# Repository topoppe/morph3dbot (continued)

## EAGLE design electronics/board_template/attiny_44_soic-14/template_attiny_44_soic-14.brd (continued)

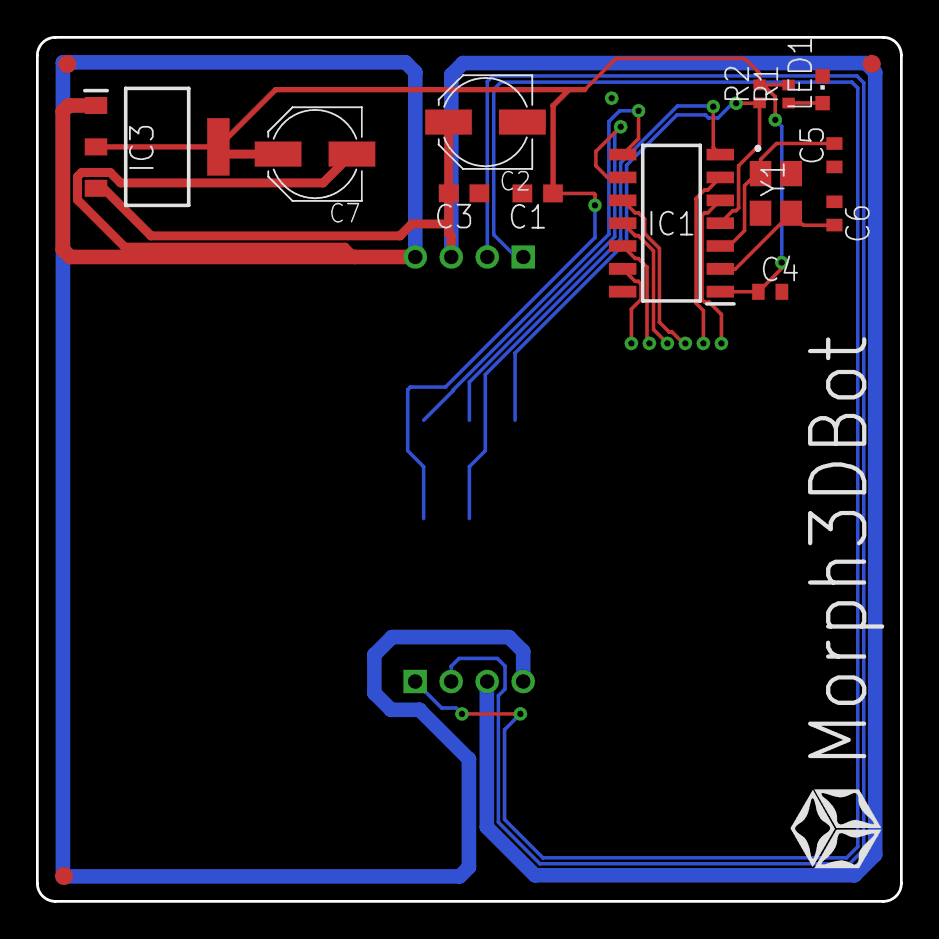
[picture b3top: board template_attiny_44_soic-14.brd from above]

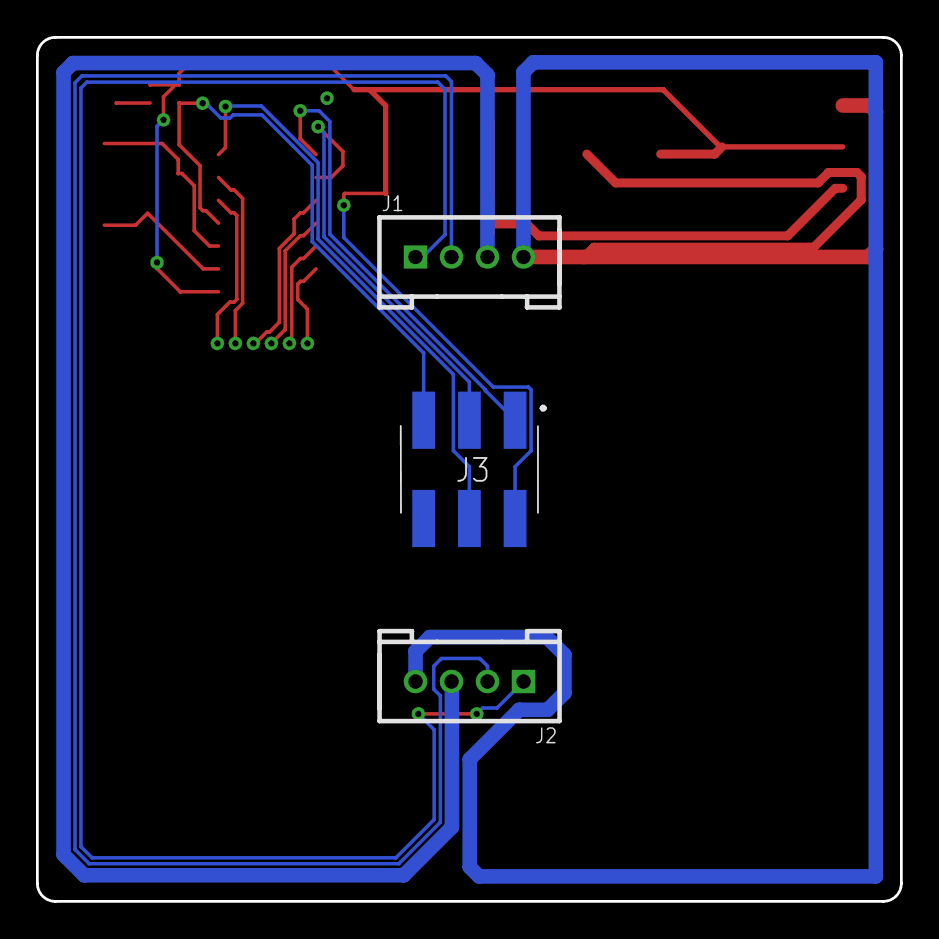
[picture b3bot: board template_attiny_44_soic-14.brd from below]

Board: 2 copper layers, 48.0 x 48.0 mm, 20 parts (3 on the bottom side), 12 nets.

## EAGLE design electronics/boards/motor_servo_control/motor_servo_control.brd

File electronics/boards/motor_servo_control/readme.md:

# Motor- und Servoplatine
Die Motor- und Servoplatine besitzt keinen eigenen Controller. Statt ihrer ist ein I2C-Portexpander [PCA9685](https://www.nxp.com/docs/en/data-sheet/PCA9685.pdf) von NXP verbaut.
Die I2C-Adresse lässt sich über einen DIP-Schalter einstellen.

Die Servo-Anschlüsse sind mit den Ausgängen LED8 bis LED15 verbunden.
Über der Anschlussleiste der Servos kann man mit Hilfe eines Jumpers einstellen, ob die Servos mit Systemspannung oder mit 5V versorgt werden sollen.

Auf der Motor-Platine ist außerdem noch ein Motortreiber [TB6612FNG](https://toshiba.semicon-storage.com/info/docget.jsp?did=10660&prodName=TB6612FNG) von Toshiba verbaut.
An ihm können zwei Gleichstrommotoren angeschlossen werden. Die Verbindung zum Portexpander-Chip lautet:

- TB6612FNG PWM-A = PCA9685 PWM2
- TB6612FNG A-IN-1 = PCA9685 PWM4
- TB6612FNG A-IN-2 = PCA9685 PWM3
- TB6612FNG PWM-B = PCA9685 PWM7
- TB6612FNG B-IN-1 = PCA9685 PWM6
- TB6612FNG B-IN-2 = PCA9685 PWM5

Die DC-Motoren werden hierbei duch die Systemspannung versorgt.

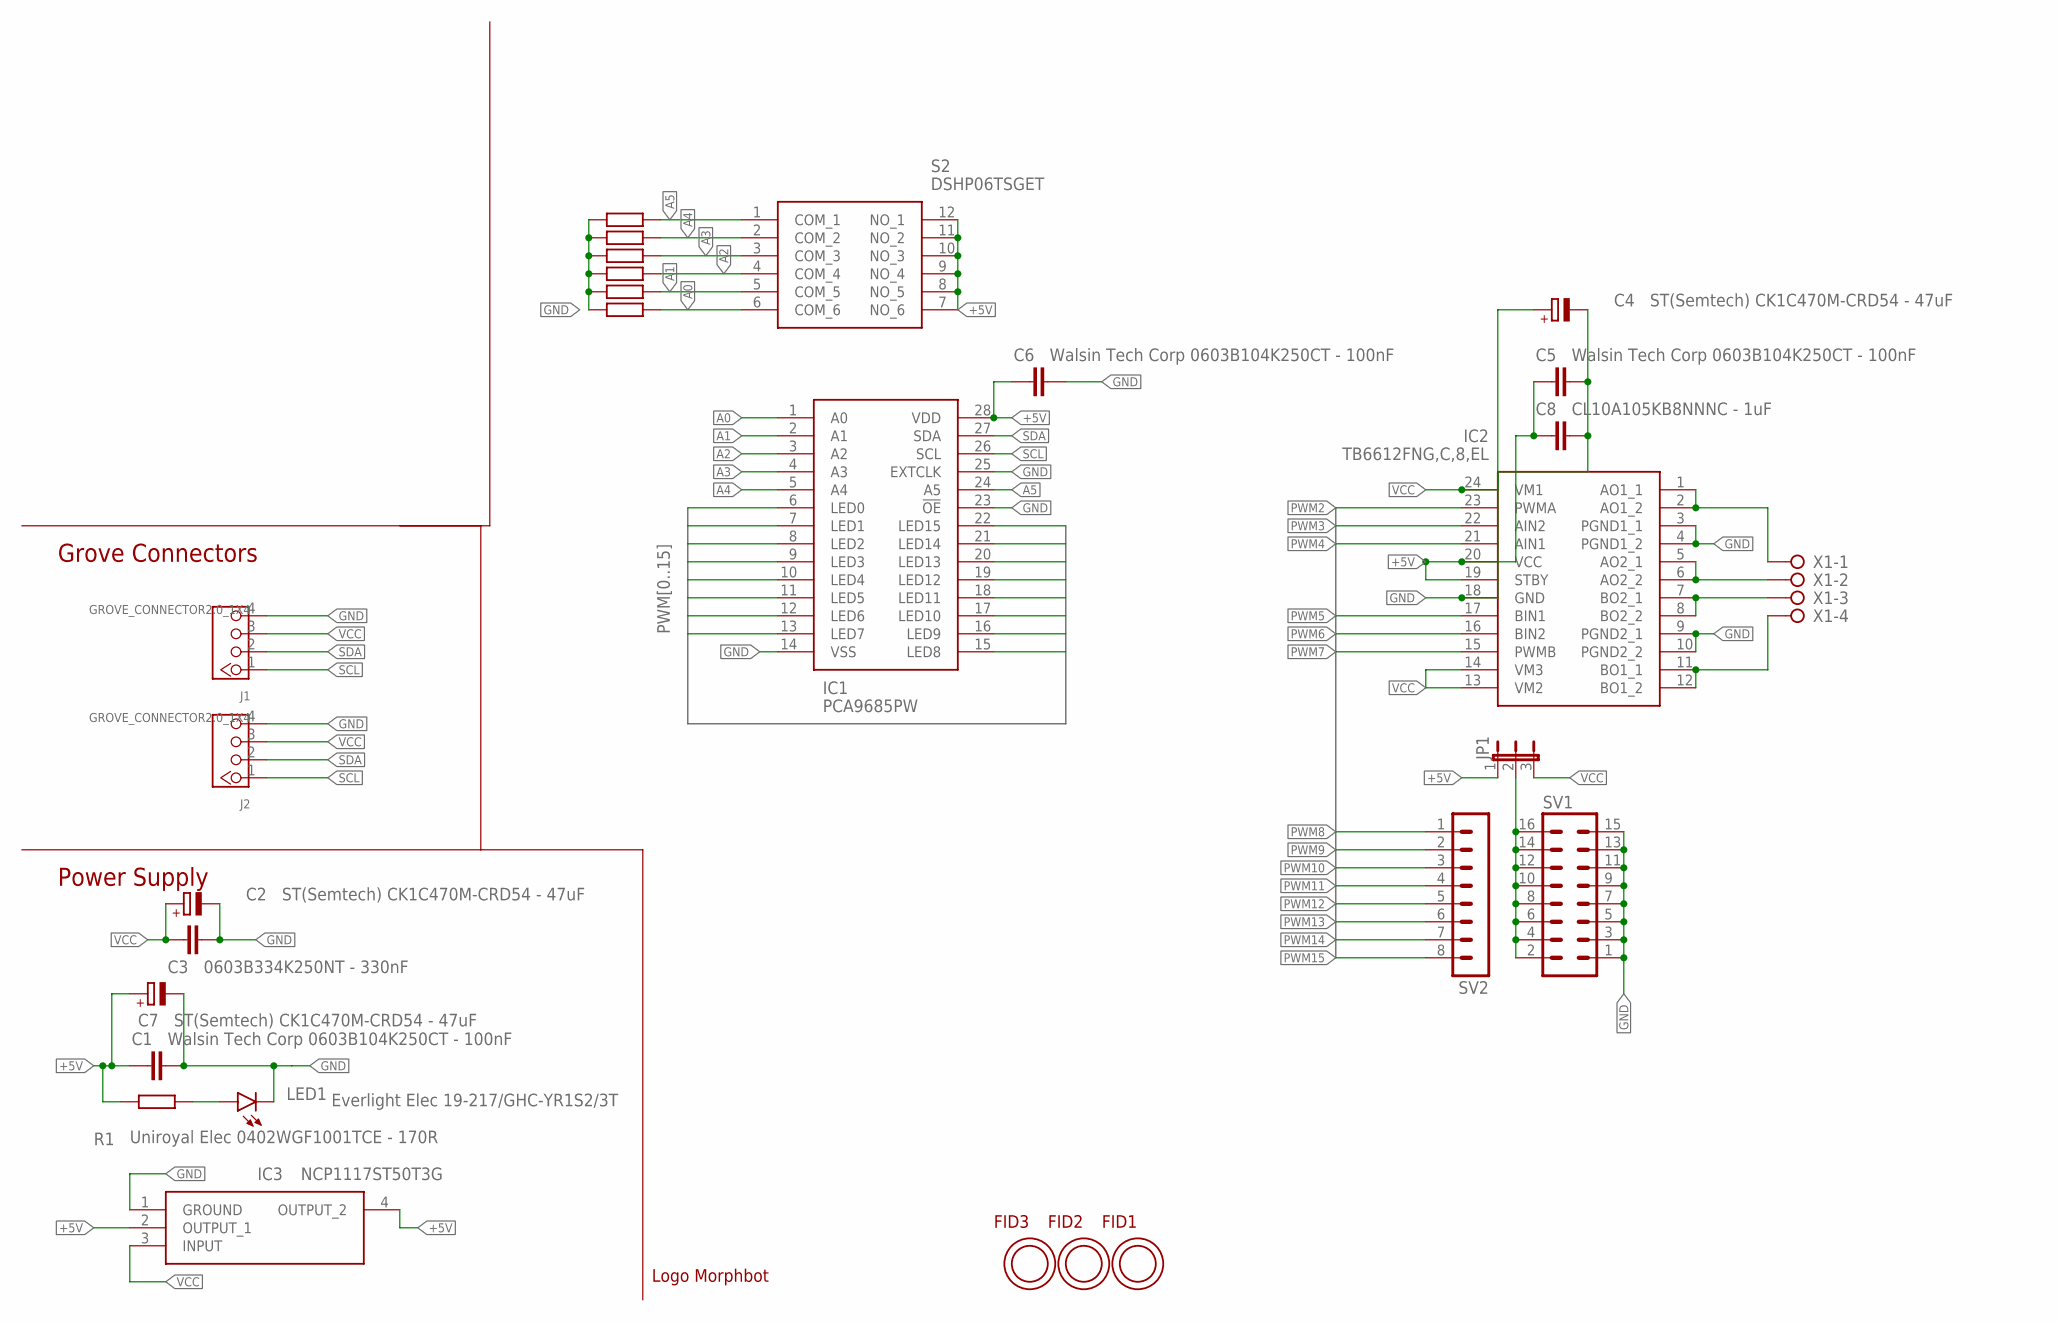
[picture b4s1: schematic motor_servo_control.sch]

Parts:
C1, C5, C6: Walsin Tech Corp 0603B104K250CT - 100nF; C0603
C2, C4, C7: ST(Semtech) CK1C470M-CRD54 - 47uF; PANASONIC_C
C3: 0603B334K250NT - 330nF; C0603
C8: CL10A105KB8NNNC - 1uF; C0603
FID1, FID2, FID3: OPEN-PNP-FIDUCIAL
IC1: PCA9685PW; SOP65P640X110-28N
IC2: TB6612FNG,C,8,EL; SOP65P760X160-24N
IC3: NCP1117ST50T3G; SOT230P700X180-4N
J1, J2: GROVE_CONNECTOR2.0_1X4; 2.0_1X4_STRAIGHT
JP1: JP2E; JP2
LED1: Everlight Elec 19-217/GHC-YR1S2/3T; CHIPLED_0603
R1: Uniroyal Elec 0402WGF1001TCE - 170R; R0402
R2, R3, R4, R5, R6, R7: 0402WGF1002TCE - 10k; R0402
S2: DSHP06TSGET
SV1: MA08-2
SV2: MA08-1
U$1: LOGO_MORPHBOT5MM; LOGO_MORPHBOT
X1: W237-04P; W237-4P

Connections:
+5V: C1.1, C5.1, C6.1, C7.+, C8.1, IC1.28 (VDD), IC2.19 (STBY), IC2.20 (VCC), IC3.2 (OUTPUT_1), IC3.4 (OUTPUT_2), JP1.1, R1.2, S2.7 (NO_6), S2.8 (NO_5), S2.9 (NO_4), S2.10 (NO_3), S2.11 (NO_2), S2.12 (NO_1)
A0: IC1.1 (A0), R7.1, S2.6 (COM_6)
A1: IC1.2 (A1), R6.1, S2.5 (COM_5)
A2: IC1.3 (A2), R5.1, S2.4 (COM_4)
A3: IC1.4 (A3), R4.1, S2.3 (COM_3)
A4: IC1.5 (A4), R3.1, S2.2 (COM_2)
A5: IC1.24 (A5), R2.1, S2.1 (COM_1)
GND: C1.2, C2.-, C3.1, C4.-, C5.2, C6.2, C7.-, C8.2, IC1.14 (VSS), IC1.23 (!OE), IC1.25 (EXTCLK), IC2.3 (PGND1_1), IC2.4 (PGND1_2), IC2.9 (PGND2_1), IC2.10 (PGND2_2), IC2.18 (GND), IC3.1 (GROUND), J1.4, J2.4, LED1.C, R2.2, R3.2, R4.2, R5.2, R6.2, R7.2, SV1.1, SV1.3, SV1.5, SV1.7, SV1.9, SV1.11, SV1.13, SV1.15
M1+: IC2.1 (AO1_1), IC2.2 (AO1_2), X1.1
M1-: IC2.5 (AO2_1), IC2.6 (AO2_2), X1.2
M2+: IC2.7 (BO2_1), IC2.8 (BO2_2), X1.3
M2-: IC2.11 (BO1_1), IC2.12 (BO1_2), X1.4
unnamed: LED1.A, R1.1
unnamed: JP1.2, SV1.2, SV1.4, SV1.6, SV1.8, SV1.10, SV1.12, SV1.14, SV1.16
PWM0: IC1.6 (LED0)
PWM1: IC1.7 (LED1)
PWM2: IC1.8 (LED2), IC2.23 (PWMA)
PWM3: IC1.9 (LED3), IC2.22 (AIN2)
PWM4: IC1.10 (LED4), IC2.21 (AIN1)
PWM5: IC1.11 (LED5), IC2.17 (BIN1)
PWM6: IC1.12 (LED6), IC2.16 (BIN2)
PWM7: IC1.13 (LED7), IC2.15 (PWMB)
PWM8: IC1.15 (LED8), SV2.1
PWM9: IC1.16 (LED9), SV2.2
PWM10: IC1.17 (LED10), SV2.3
PWM11: IC1.18 (LED11), SV2.4
PWM12: IC1.19 (LED12), SV2.5
PWM13: IC1.20 (LED13), SV2.6
PWM14: IC1.21 (LED14), SV2.7
PWM15: IC1.22 (LED15), SV2.8
SCL: IC1.26 (SCL), J1.1, J2.1
SDA: IC1.27 (SDA), J1.2, J2.2
VCC: C2.+, C3.2, C4.+, IC2.13 (VM2), IC2.14 (VM3), IC2.24 (VM1), IC3.3 (INPUT), J1.3, J2.3, JP1.3

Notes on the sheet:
Power Supply
Grove Connectors

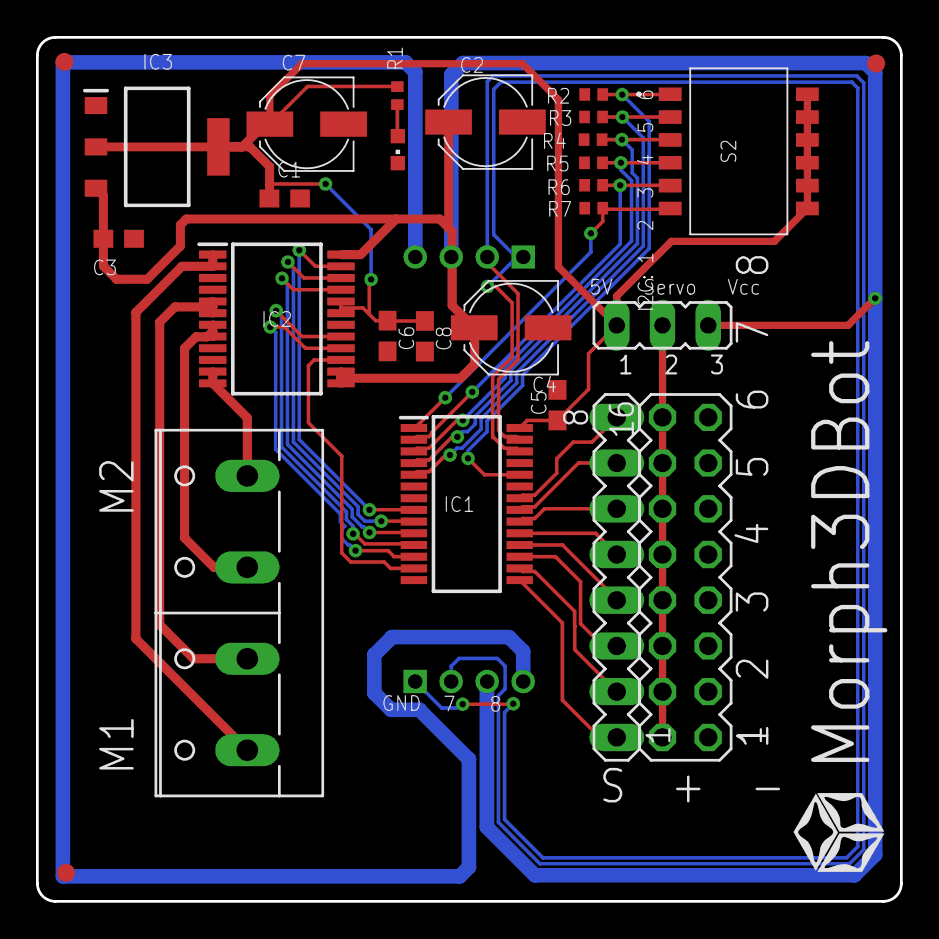
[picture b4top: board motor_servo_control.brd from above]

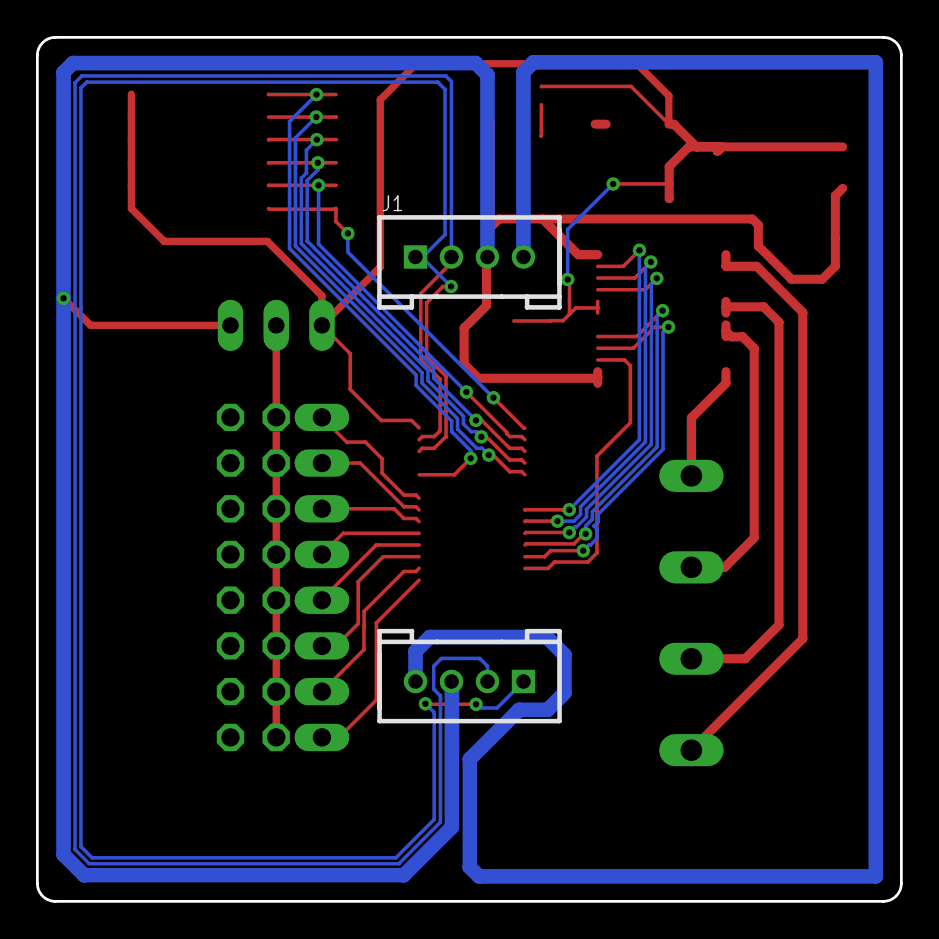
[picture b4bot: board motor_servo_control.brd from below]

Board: 2 copper layers, 48.0 x 48.0 mm, 30 parts (2 on the bottom side), 31 nets.

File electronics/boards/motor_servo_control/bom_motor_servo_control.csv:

"Qty";"Value";"Device";"Package";"Parts";"Description";"ARROW_PART_NUMBER";"ARROW_PRICE-STOCK";"DESCRIPTION";"HEIGHT";"MANUFACTURER_NAME";"MANUFACTURER_PART_NUMBER";"MF";"MOUSER_PART_NUMBER";"MOUSER_PRICE-STOCK";"MPN";"OC_FARNELL";"OC_NEWARK";"POPULARITY";"SPICEPREFIX";
"1";"";"JP2E";"JP2";"JP1";"JUMPER";"";"";"";"";"";"";"";"";"";"";"";"";"34";"";
"1";"";"MA08-1";"MA08-1";"SV2";"PIN HEADER";"";"";"";"";"";"";"";"";"";"";"unknown";"unknown";"10";"";
"1";"";"MA08-2";"MA08-2";"SV1";"PIN HEADER";"";"";"";"";"";"";"";"";"";"";"unknown";"unknown";"0";"";
"1";"";"W237-04P";"W237-4P";"X1";"WAGO SREW CLAMP";"";"";"";"";"";"";"";"";"";"";"unknown";"unknown";"2";"";
"6";"0402WGF1002TCE - 10k";"R-EU_R0402";"R0402";"R2, R3, R4, R5, R6, R7";"RESISTOR, European symbol";"";"";"";"";"";"";"";"";"";"";"";"";"0";"R";
"1";"0603B334K250NT - 330nF";"C-EUC0603";"C0603";"C3";"CAPACITOR, European symbol";"";"";"";"";"";"";"";"";"";"";"";"";"73";"C";
"1";"CL10A105KB8NNNC - 1uF";"C-EUC0603";"C0603";"C8";"CAPACITOR, European symbol";"";"";"";"";"";"";"";"";"";"";"";"";"73";"C";
"1";"DSHP06TSGET";"DSHP06TSGET";"DSHP06TSGET";"S2";"SPST 6 1.27mm, Half Slide (Standard) Black SMD DIP Switches";"";"";"SPST 6 1.27mm, Half Slide (Standard) Black SMD DIP Switches";"2.6mm";"Dongguan Guangzhu Industrial";"DSHP06TSGET";"";"";"";"";"";"";"";"";
"1";"Everlight Elec 19-217/GHC-YR1S2/3T";"LEDCHIPLED_0603";"CHIPLED_0603";"LED1";"LED";"";"";"";"";"";"";"";"";"";"";"";"";"28";"";
"2";"GROVE_CONNECTOR2.0_1X4";"GROVE_CONNECTOR2.0_1X4";"2.0_1X4_STRAIGHT";"J1, J2";"Seeedstudio Grove-Connector:";"";"";"";"";"";"";"";"";"";"";"";"";"";"";
"1";"LOGO_MORPHBOT5MM";"LOGO_MORPHBOT5MM";"LOGO_MORPHBOT";"U$1";"";"";"";"";"";"";"";"";"";"";"";"";"";"";"";
"1";"NCP1117ST50T3G";"NCP1117ST50T3G";"SOT230P700X180-4N";"IC3";"ON SEMICONDUCTOR - NCP1117ST50T3G - LDO, REG, 20VIN, 1A, 5V, 1%, SOT223-3";"NCP1117ST50T3G";"https://www.arrow.com/en/products/ncp1117st50t3g/on-semiconductor";"ON SEMICONDUCTOR - NCP1117ST50T3G - LDO, REG, 20VIN, 1A, 5V, 1%, SOT223-3";"1.8mm";"ON Semiconductor";"NCP1117ST50T3G";"";"863-NCP1117ST50T3G";"https://www.mouser.co.uk/ProductDetail/ON-Semiconductor/NCP1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";"";"";"";"";"";
"3";"OPEN-PNP-FIDUCIAL";"OPEN-PNP-FIDUCIAL";"OPEN-PNP-FIDUCIAL";"FID1, FID2, FID3";"";"";"";"";"";"";"";"";"";"";"";"";"";"";"";
"1";"PCA9685PW";"PCA9685PW";"SOP65P640X110-28N";"IC1";"LED DRIVER, RGBA, 28-TSSOP";"";"";"LED DRIVER, RGBA, 28-TSSOP";"1.1mm";"Nexperia";"PCA9685PW";"";"N/A";"https://www.mouser.com/Search/Refine.aspx?Keyword=N%2FA";"";"";"";"";"";
"3";"ST(Semtech) CK1C470M-CRD54 - 47uF";"CPOL-EUC";"PANASONIC_C";"C2, C4, C7";"POLARIZED CAPACITOR, European symbol";"";"";"";"";"";"";"";"";"";"";"";"";"4";"C";
"1";"TB6612FNG,C,8,EL";"TB6612FNG,C,8,EL";"SOP65P760X160-24N";"IC2";"otor / Motion / Ignition Controllers & Drivers Brush Motor Driver IC";"TB6612FNG,C,8,EL";"https://www.arrow.com/en/products/tb6612fngc8el/toshiba";"otor / Motion / Ignition Controllers & Drivers Brush Motor Driver IC";"1.6mm";"Toshiba";"TB6612FNG,C,8,EL";"";"757-TB6612FNGC8EL";"https://www.mouser.co.uk/ProductDetail/Toshiba/TB6612FNGC8EL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";"";"";"";"";"";
"1";"Uniroyal Elec 0402WGF1001TCE - 170R";"R-EU_R0402";"R0402";"R1";"RESISTOR, European symbol";"";"";"";"";"";"";"";"";"";"";"";"";"0";"R";
"3";"Walsin Tech Corp 0603B104K250CT - 100nF";"C-EUC0603";"C0603";"C1, C5, C6";"CAPACITOR, European symbol";"";"";"";"";"";"";"";"";"";"";"";"";"73";"C";

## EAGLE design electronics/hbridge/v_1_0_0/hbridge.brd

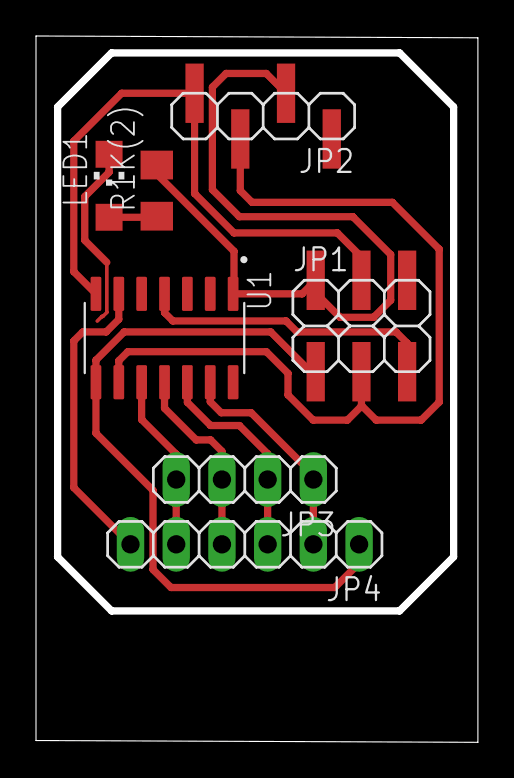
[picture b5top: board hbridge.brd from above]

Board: 2 copper layers, 24.6 x 39.2 mm, 7 parts (0 on the bottom side), 12 nets.

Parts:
JP1: 2X03SMD
JP2: 1X04SMD
JP3: 1X04
JP4: 1X06
LED1: CHIPLED_1206
R1K(2): R1206
U1: ATTINY44A-SSU; SOIC127P600X175-14N

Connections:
GND: JP1.6, JP2.1, LED1.C, U1.14
unnamed: JP3.1, JP4.2, U1.13
unnamed: JP3.2, JP4.3, U1.12
unnamed: LED1.A, R1K(2).1
unnamed: JP1.4, JP2.4, U1.7
unnamed: JP3.3, JP4.4, U1.11
unnamed: JP1.1, JP4.1, U1.8
unnamed: JP3.4, JP4.5, U1.10
unnamed: JP4.6, U1.6
unnamed: JP1.5, U1.4
unnamed: JP1.3, JP2.3, U1.9
VCC: JP1.2, JP2.2, R1K(2).2, U1.1

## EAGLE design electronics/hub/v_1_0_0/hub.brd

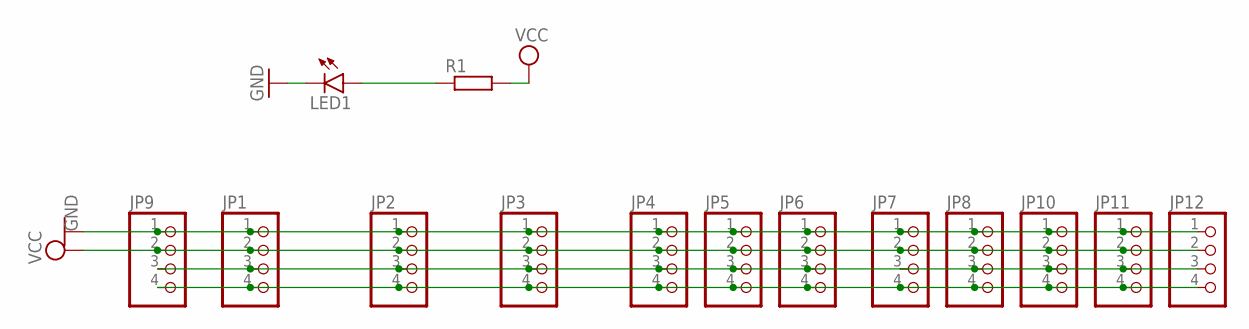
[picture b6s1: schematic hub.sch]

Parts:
JP1, JP2, JP3, JP4, JP5, JP6, JP7, JP8, JP9, JP10, JP11, JP12: PINHD-1X04_2.54-SMD; 1X04SMD
LED1: LEDCHIPLED_1206; CHIPLED_1206
R1: R-EU_R1206; R1206

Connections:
GND: JP1.1, JP2.1, JP3.1, JP4.1, JP5.1, JP6.1, JP7.1, JP8.1, JP9.1, JP10.1, JP11.1, JP12.1, LED1.C
unnamed: JP1.3, JP2.3, JP3.3, JP4.3, JP5.3, JP6.3, JP7.3, JP8.3, JP9.3, JP10.3, JP11.3, JP12.3
unnamed: JP1.4, JP2.4, JP3.4, JP4.4, JP5.4, JP6.4, JP7.4, JP8.4, JP9.4, JP10.4, JP11.4, JP12.4
unnamed: LED1.A, R1.1
VCC: JP1.2, JP2.2, JP3.2, JP4.2, JP5.2, JP6.2, JP7.2, JP8.2, JP9.2, JP10.2, JP11.2, JP12.2, R1.2

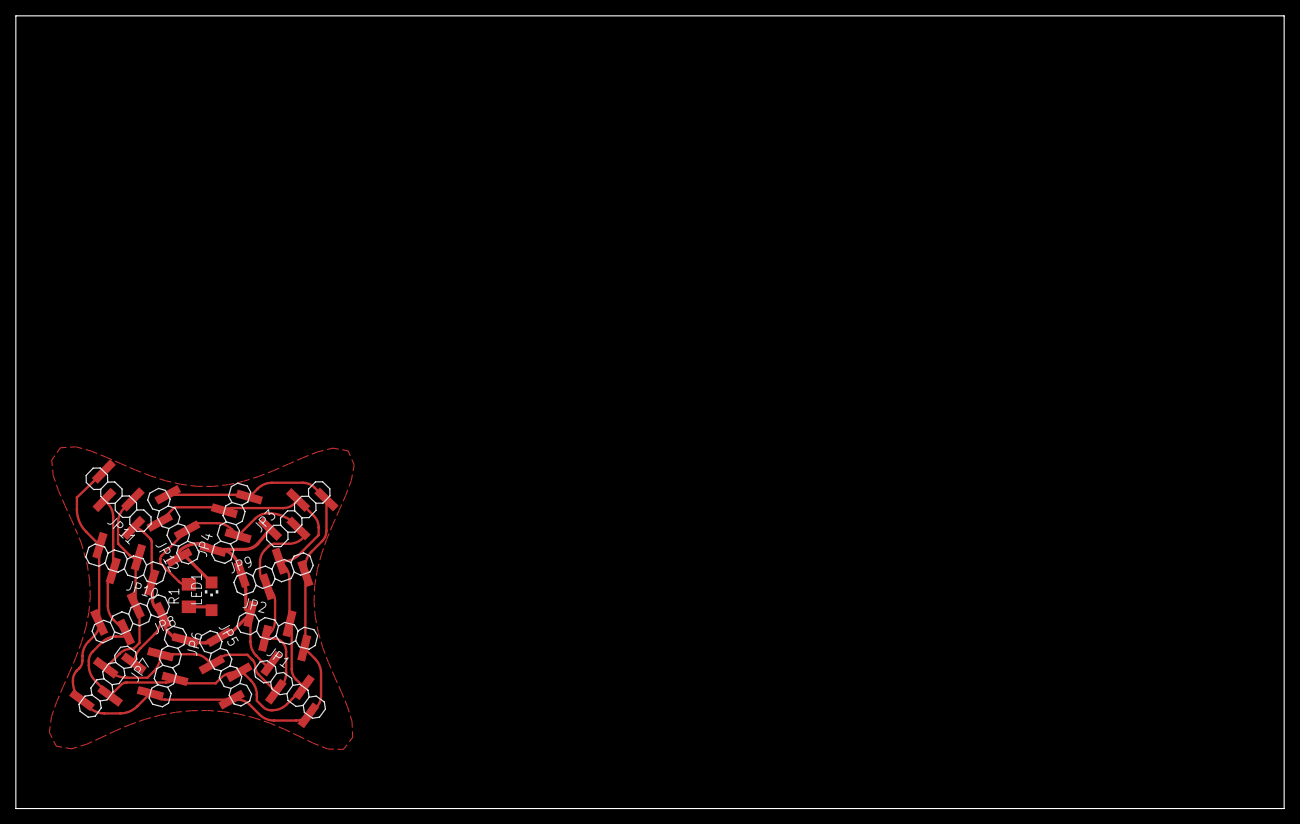
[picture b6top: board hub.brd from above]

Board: 2 copper layers, 160.0 x 100.0 mm, 14 parts (0 on the bottom side), 5 nets.

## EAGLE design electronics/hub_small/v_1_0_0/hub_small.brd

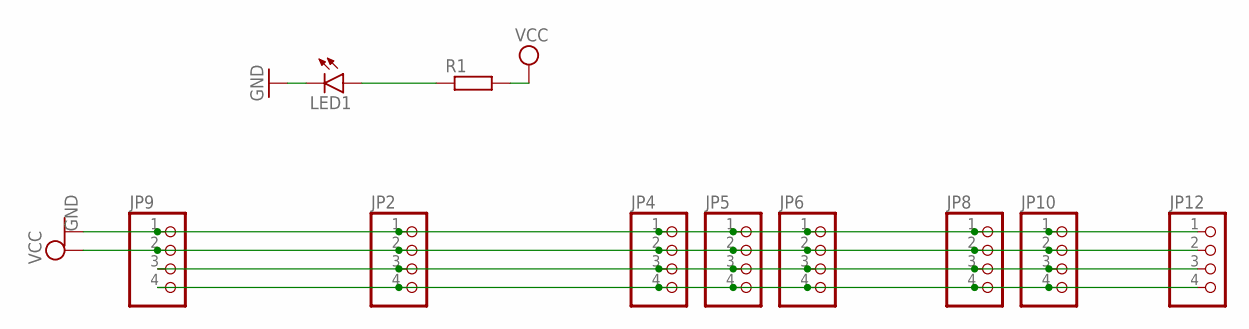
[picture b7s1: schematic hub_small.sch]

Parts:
JP2, JP4, JP5, JP6, JP8, JP9, JP10, JP12: PINHD-1X04_2.54-SMD; 1X04SMD
LED1: LEDCHIPLED_1206; CHIPLED_1206
R1: R-EU_R1206; R1206

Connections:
GND: JP2.1, JP4.1, JP5.1, JP6.1, JP8.1, JP9.1, JP10.1, JP12.1, LED1.C
unnamed: JP2.4, JP4.4, JP5.4, JP6.4, JP8.4, JP9.4, JP10.4, JP12.4
unnamed: LED1.A, R1.1
unnamed: JP2.3, JP4.3, JP5.3, JP6.3, JP8.3, JP9.3, JP10.3, JP12.3
VCC: JP2.2, JP4.2, JP5.2, JP6.2, JP8.2, JP9.2, JP10.2, JP12.2, R1.2

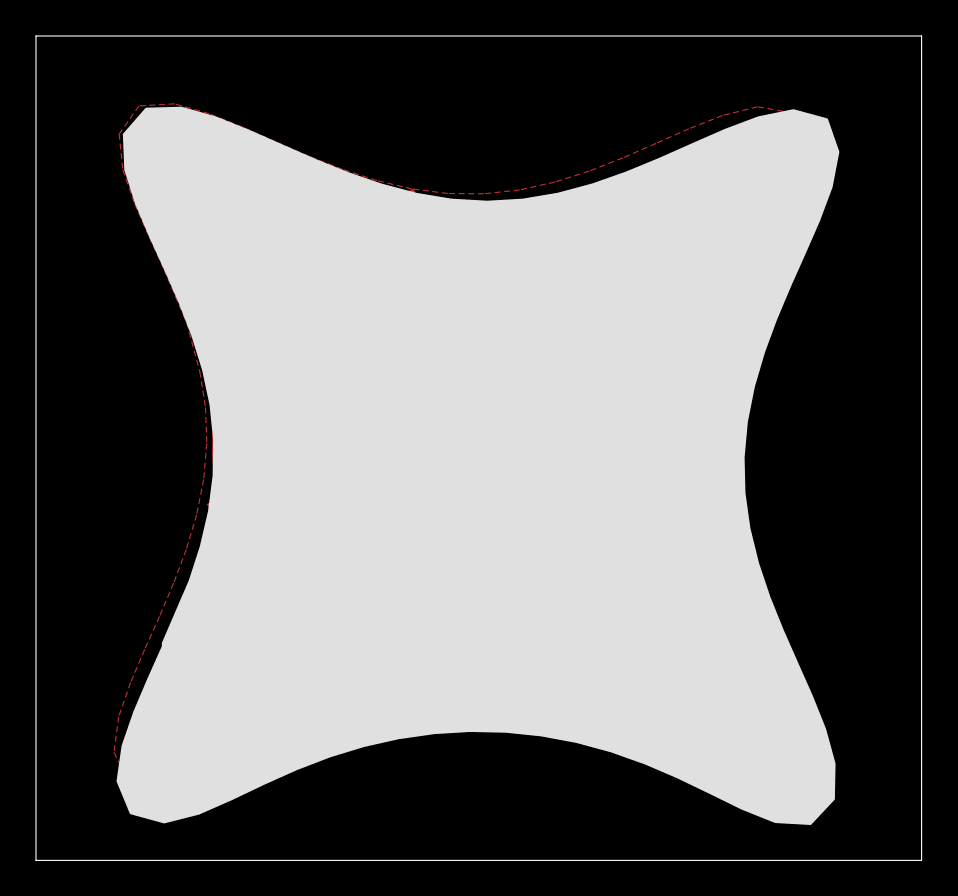
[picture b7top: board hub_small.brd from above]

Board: 2 copper layers, 49.2 x 45.8 mm, 10 parts (0 on the bottom side), 5 nets.
